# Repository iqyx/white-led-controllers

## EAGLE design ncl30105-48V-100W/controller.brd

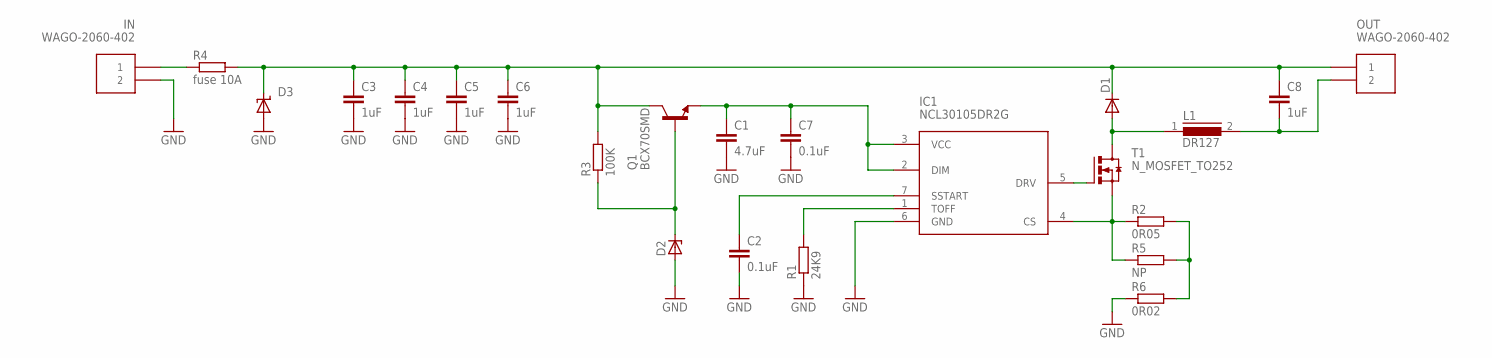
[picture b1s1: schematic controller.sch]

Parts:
C1: 4.7uF; C0805
C2: 0.1uF; C0603
C3, C4, C5, C6, C8: 1uF; C1210
C7: 0.1uF; C0805
D1: DIODE-SMC; SMC
D2: ZENER-DIODESOT23; SOT23
D3: SUPPRESSOR-SMBJ; SMBJ
IC1: NCL30105DR2G; SOIC8
IN: WAGO-2060-402
L1: DR127
OUT: WAGO-2060-402
Q1: BCX70SMD; SOT23
R1: 24K9; R0603
R2: 0R05; R1210
R3: 100K; R1206
R4: fuse 10A; R1206
R5: NP; R1210
R6: 0R02; R1210
T1: N_MOSFET_TO252; TO252

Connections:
GND: C1.2, C2.2, C3.2, C4.2, C5.2, C6.2, C7.2, D2.1 (A), D3.A, IC1.6 (GND), IN.2_1 (2), IN.2_2 (2), R1.1, R6.1
unnamed: IC1.5 (DRV), T1.1 (G)
unnamed: C2.1, IC1.7 (SSTART)
unnamed: IC1.4 (CS), R2.1, R5.1, T1.3 (S)
unnamed: R2.2, R5.2, R6.2
unnamed: D1.A, L1.1, T1.4 (D)
unnamed: IC1.1 (TOFF), R1.2
unnamed: C8.2, L1.2, OUT.2_1 (2), OUT.2_2 (2)
unnamed: C1.1, C7.1, IC1.2 (DIM), IC1.3 (VCC), Q1.2 (E)
unnamed: D2.3 (C), Q1.1 (B), R3.1
unnamed: IN.1_1 (1), IN.1_2 (1), R4.1
VIN: C3.1, C4.1, C5.1, C6.1, C8.1, D1.C, D3.C, OUT.1_1 (1), OUT.1_2 (1), Q1.3 (C), R3.2, R4.2

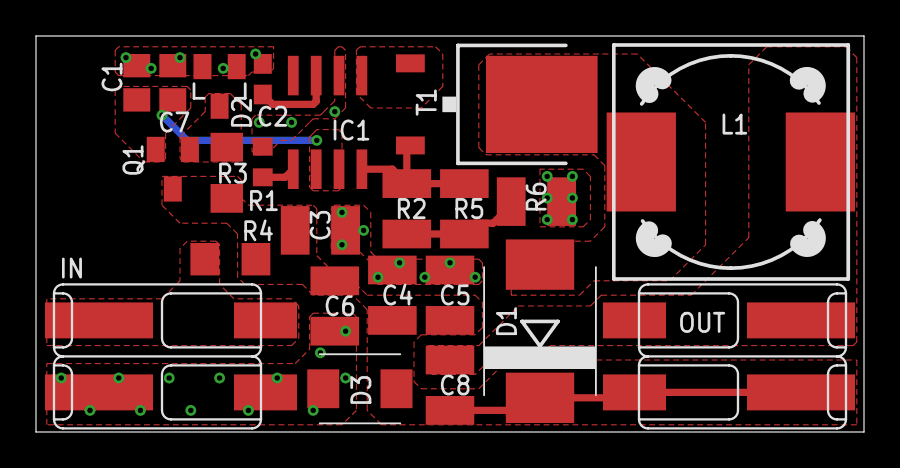
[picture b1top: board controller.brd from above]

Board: 2 copper layers, 46.0 x 22.0 mm, 23 parts (0 on the bottom side), 12 nets.

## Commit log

2015-09-25 Add NCL30105 48V 100W LED driver.
2015-11-06 Finish rev1.0 changes
